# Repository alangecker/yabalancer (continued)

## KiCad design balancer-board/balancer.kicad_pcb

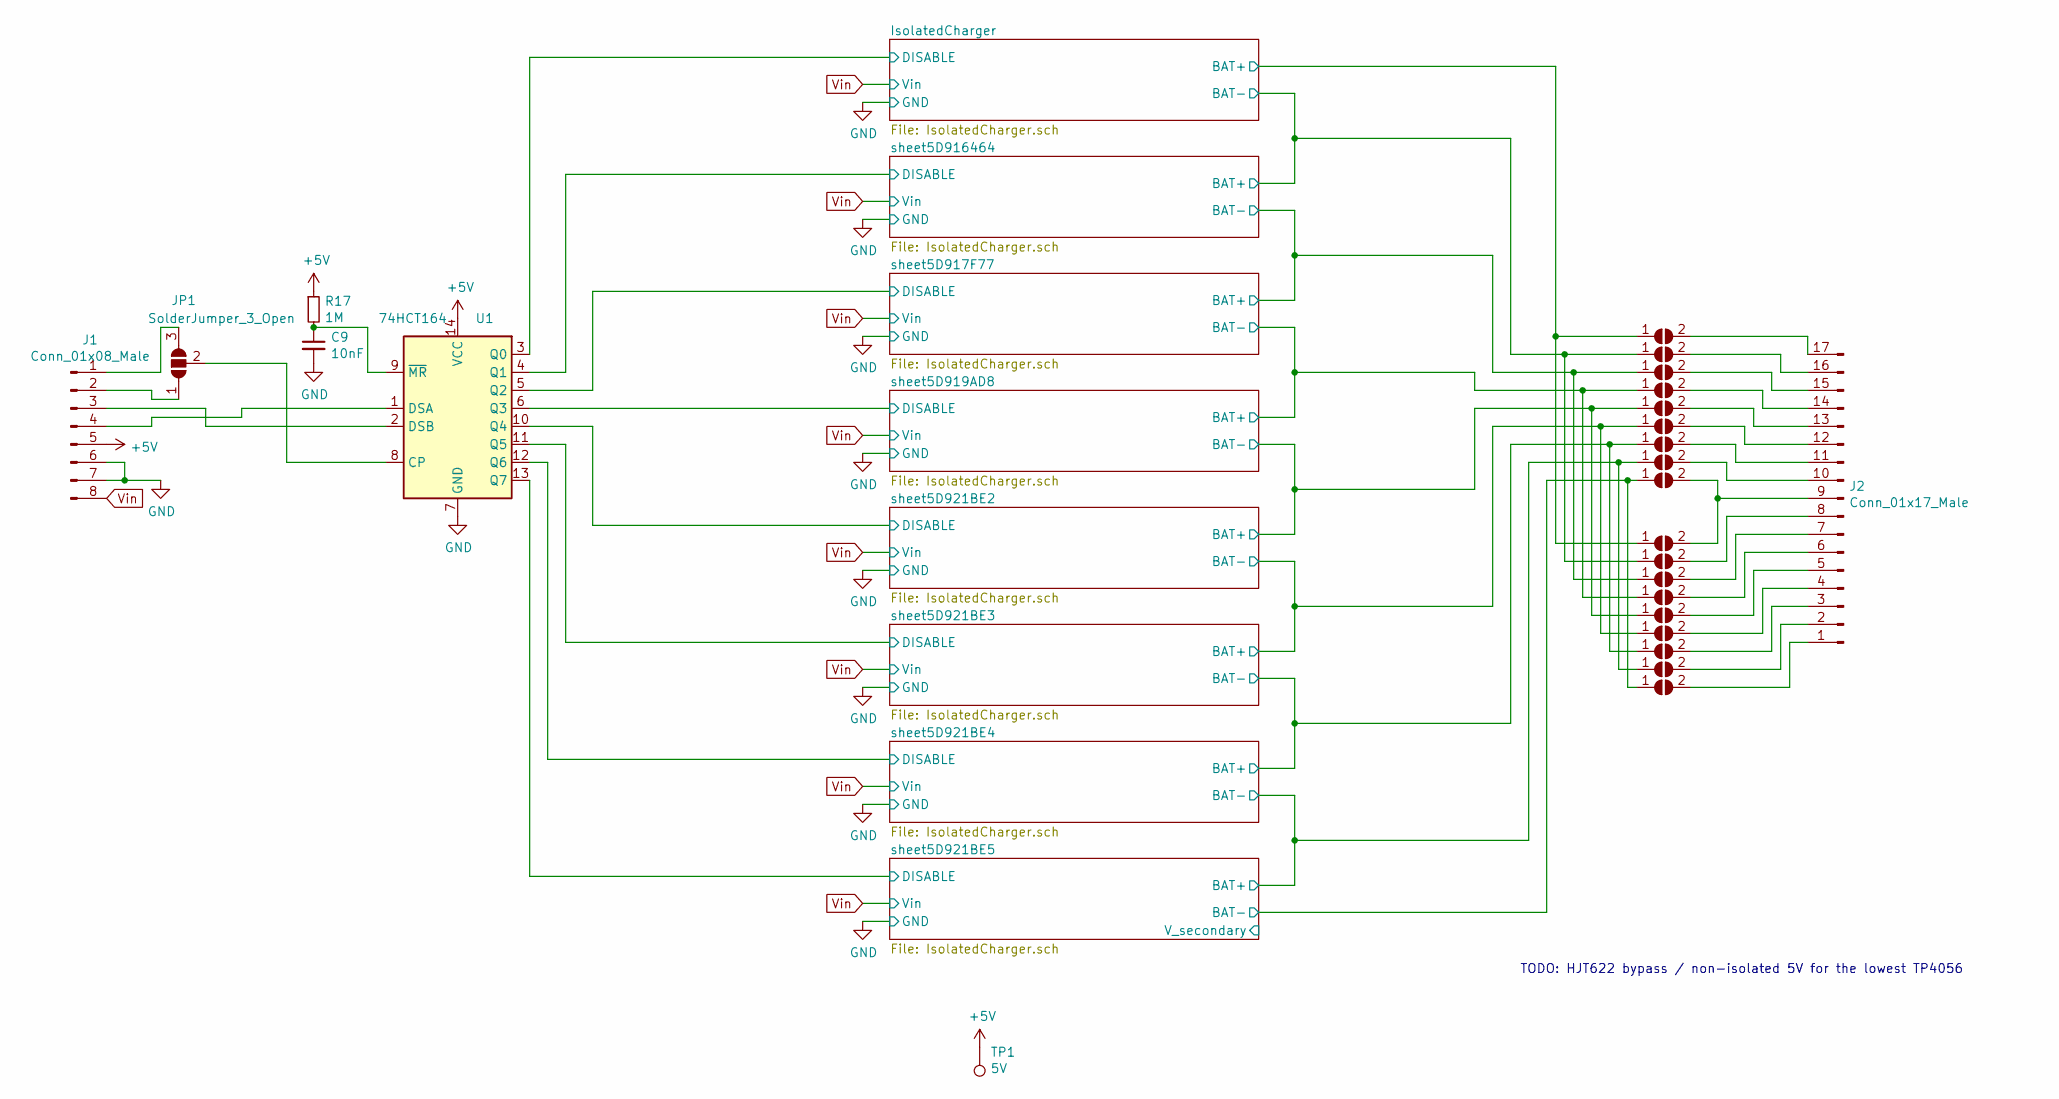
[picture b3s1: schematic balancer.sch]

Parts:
C9: 10nF; C_0805_2012Metric_Pad1.15x1.40mm_HandSolder
J1: Conn_01x08_Male; PinHeader_1x08_P2.54mm_Vertical
J2: Conn_01x17_Male; PinHeader_1x17_P2.54mm_Vertical
JP1: SolderJumper_3_Open; SolderJumper-3_P1.3mm_Open_RoundedPad1.0x1.5mm
JP2, JP3, JP4, JP5, JP6, JP7, JP8, JP9, JP10, JP11, JP12, JP13, JP14, JP15, JP16, JP17, JP18, JP19: SolderJumper_2_Open; SolderJumper-2_P1.3mm_Open_Pad1.0x1.5mm
R17: 1M; R_0805_2012Metric_Pad1.15x1.40mm_HandSolder
TP1: 5V; TestPoint_THTPad_2.5x2.5mm_Drill1.2mm
U1: 74HCT164; SO-14

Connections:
+5V: J1.5, R17.1, TP1.1, U1.14 (VCC)
/IsolatedCharger/BAT+: JP2.1 (A), JP11.1 (A); also elsewhere on the board
/IsolatedCharger/DISABLE: U1.3 (Q0); also elsewhere on the board
/sheet5D917F77/BAT+: JP4.1 (A), JP13.1 (A); also elsewhere on the board
/sheet5D917F77/DISABLE: U1.5 (Q2); also elsewhere on the board
/sheet5D919AD8/BAT+: JP5.1 (A), JP14.1 (A); also elsewhere on the board
/sheet5D919AD8/DISABLE: U1.6 (Q3); also elsewhere on the board
/sheet5D921BE2/BAT+: JP6.1 (A), JP15.1 (A); also elsewhere on the board
/sheet5D921BE2/DISABLE: U1.10 (Q4); also elsewhere on the board
/sheet5D921BE3/BAT+: JP7.1 (A), JP16.1 (A); also elsewhere on the board
/sheet5D921BE3/DISABLE: U1.11 (Q5); also elsewhere on the board
/sheet5D921BE4/BAT+: JP8.1 (A), JP17.1 (A); also elsewhere on the board
/sheet5D921BE4/DISABLE: U1.12 (Q6); also elsewhere on the board
/sheet5D921BE5/BAT+: JP9.1 (A), JP18.1 (A); also elsewhere on the board
/sheet5D921BE5/BAT-: JP10.1 (A), JP19.1 (A); also elsewhere on the board
/sheet5D921BE5/DISABLE: U1.13 (Q7); also elsewhere on the board
/sheet5D916464/BAT+: JP3.1 (A), JP12.1 (A); also elsewhere on the board
/sheet5D916464/DISABLE: U1.4 (Q1); also elsewhere on the board
GND: C9.2, J1.6, J1.7, U1.7 (GND); also elsewhere on the board
unnamed: C9.1, R17.2, U1.9 (~MR)
unnamed: J1.1, JP1.3 (B)
unnamed: J1.2, JP1.1 (A)
unnamed: J1.3, U1.2 (DSB)
unnamed: J1.4, U1.1 (DSA)
unnamed: J2.1, JP19.2 (B)
unnamed: J2.2, JP18.2 (B)
unnamed: J2.3, JP17.2 (B)
unnamed: J2.4, JP16.2 (B)
unnamed: J2.5, JP15.2 (B)
unnamed: J2.6, JP14.2 (B)
unnamed: J2.7, JP13.2 (B)
unnamed: J2.8, JP12.2 (B)
unnamed: J2.9, JP10.2 (B), JP11.2 (B)
unnamed: J2.10, JP9.2 (B)
unnamed: J2.11, JP8.2 (B)
unnamed: J2.12, JP7.2 (B)
unnamed: J2.13, JP6.2 (B)
unnamed: J2.14, JP5.2 (B)
unnamed: J2.15, JP4.2 (B)
unnamed: J2.16, JP3.2 (B)
unnamed: J2.17, JP2.2 (B)
unnamed: JP1.2 (C), U1.8 (CP)
Vin: J1.8; also elsewhere on the board

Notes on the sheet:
TODO: HJT622 bypass / non-isolated 5V for the lowest TP4056

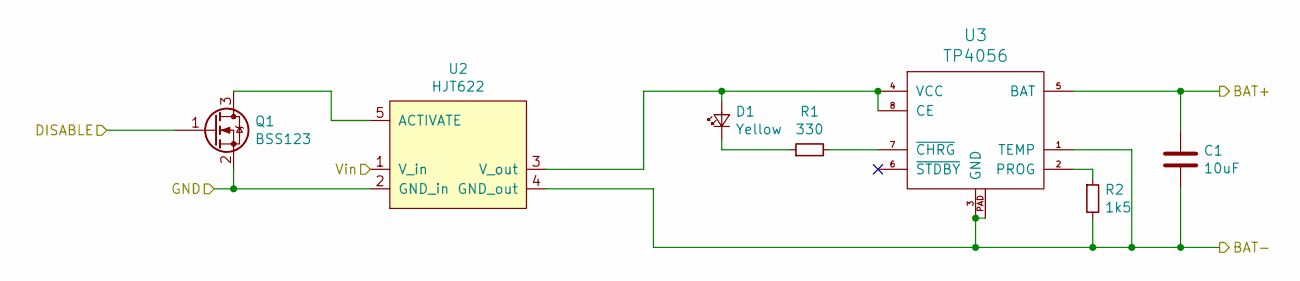
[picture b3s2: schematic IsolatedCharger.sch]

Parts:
C1: 10uF; C_0805_2012Metric
D1: Yellow; LED_D5.0mm_Horizontal_O1.27mm_Z15.0mm
Q8: BSS123; SOT-23
R1: 330; R_0805_2012Metric
R2: 1k5; R_0805_2012Metric
U2: HJT622
U3: TP4056; SOP-8_3.76x4.96mm_P1.27mm

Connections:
/IsolatedCharger/BAT+: C1.1, U3.5 (BAT); also elsewhere on the board
/sheet5D921BE5/DISABLE: Q8.1 (G); also elsewhere on the board
/sheet5D916464/BAT+: C1.2, R2.2, U2.4 (GND_out), U3.1 (TEMP), U3.3 (GND), U3.PAD; also elsewhere on the board
GND: Q8.2 (S), U2.2 (GND_in); also elsewhere on the board
unnamed: D1.1 (K), R1.1
unnamed: D1.2 (A), U2.3 (V_out), U3.4 (VCC), U3.8 (CE)
unnamed: R1.2, U3.7 (~CHRG)
unnamed: R2.1, U3.2 (PROG)
Vin: U2.1 (V_in); also elsewhere on the board

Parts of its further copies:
C2, C3, C4, C5, C6, C7, C8: 10uF; C_0805_2012Metric
D2, D3, D4, D5, D6, D7, D8: Yellow; LED_D5.0mm_Horizontal_O1.27mm_Z15.0mm
R3, R5, R7, R9, R11, R13, R15: 330; R_0805_2012Metric
R4, R6, R8, R10, R12, R14, R16: 1k5; R_0805_2012Metric
U4, U6, U8, U10, U12, U14, U16: HJT622
U5, U7, U9, U11, U13, U15, U17: TP4056; SOP-8_3.76x4.96mm_P1.27mm

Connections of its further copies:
/sheet5D917F77/BAT+: C2.2, C3.1, R4.2, U4.4 (GND_out), U5.1 (TEMP), U5.3 (GND), U7.5 (BAT); also elsewhere on the board
/sheet5D919AD8/BAT+: C3.2, C4.1, R6.2, U6.4 (GND_out), U7.1 (TEMP), U7.3 (GND), U9.5 (BAT); also elsewhere on the board
/sheet5D921BE2/BAT+: C4.2, C5.1, R8.2, U8.4 (GND_out), U9.1 (TEMP), U9.3 (GND), U11.5 (BAT); also elsewhere on the board
/sheet5D921BE3/BAT+: C5.2, C6.1, R10.2, U10.4 (GND_out), U11.1 (TEMP), U11.3 (GND), U13.5 (BAT); also elsewhere on the board
/sheet5D921BE4/BAT+: C6.2, C7.1, R12.2, U12.4 (GND_out), U13.1 (TEMP), U13.3 (GND), U15.5 (BAT); also elsewhere on the board
/sheet5D921BE5/BAT+: C7.2, C8.1, R14.2, U14.4 (GND_out), U15.1 (TEMP), U15.3 (GND), U17.5 (BAT); also elsewhere on the board
/sheet5D921BE5/BAT-: C8.2, R16.2, U16.4 (GND_out), U17.1 (TEMP), U17.3 (GND); also elsewhere on the board
/sheet5D916464/BAT+: C2.1, U5.5 (BAT); also elsewhere on the board
GND: U4.2 (GND_in), U6.2 (GND_in), U8.2 (GND_in), U10.2 (GND_in), U12.2 (GND_in), U14.2 (GND_in), U16.2 (GND_in); also elsewhere on the board
unnamed: D2.1 (K), R3.1
unnamed: D2.2 (A), U4.3 (V_out), U5.4 (VCC), U5.8 (CE)
unnamed: D3.1 (K), R5.1
unnamed: D3.2 (A), U6.3 (V_out), U7.4 (VCC), U7.8 (CE)
unnamed: D4.1 (K), R7.1
unnamed: D4.2 (A), U8.3 (V_out), U9.4 (VCC), U9.8 (CE)
unnamed: D5.1 (K), R9.1
unnamed: D5.2 (A), U10.3 (V_out), U11.4 (VCC), U11.8 (CE)
unnamed: D6.1 (K), R11.1
unnamed: D6.2 (A), U12.3 (V_out), U13.4 (VCC), U13.8 (CE)
unnamed: D7.1 (K), R13.1
unnamed: D7.2 (A), U14.3 (V_out), U15.4 (VCC), U15.8 (CE)
unnamed: D8.1 (K), R15.1
unnamed: D8.2 (A), U16.3 (V_out), U17.4 (VCC), U17.8 (CE)
unnamed 58: U4.5 (ACTIVATE); also elsewhere on the board
unnamed 59: U6.5 (ACTIVATE); also elsewhere on the board
unnamed 60: U8.5 (ACTIVATE); also elsewhere on the board
unnamed 61: U10.5 (ACTIVATE); also elsewhere on the board
unnamed 62: U12.5 (ACTIVATE); also elsewhere on the board
unnamed 63: U14.5 (ACTIVATE); also elsewhere on the board
unnamed: R3.2, U5.7 (~CHRG)
unnamed: R4.1, U5.2 (PROG)
unnamed: R5.2, U7.7 (~CHRG)
unnamed: R6.1, U7.2 (PROG)
unnamed: R7.2, U9.7 (~CHRG)
unnamed: R8.1, U9.2 (PROG)
unnamed: R9.2, U11.7 (~CHRG)
unnamed: R10.1, U11.2 (PROG)
unnamed: R11.2, U13.7 (~CHRG)
unnamed: R12.1, U13.2 (PROG)
unnamed: R13.2, U15.7 (~CHRG)
unnamed: R14.1, U15.2 (PROG)
unnamed: R15.2, U17.7 (~CHRG)
unnamed: R16.1, U17.2 (PROG)
Vin: U4.1 (V_in), U6.1 (V_in), U8.1 (V_in), U10.1 (V_in), U12.1 (V_in), U14.1 (V_in), U16.1 (V_in); also elsewhere on the board

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
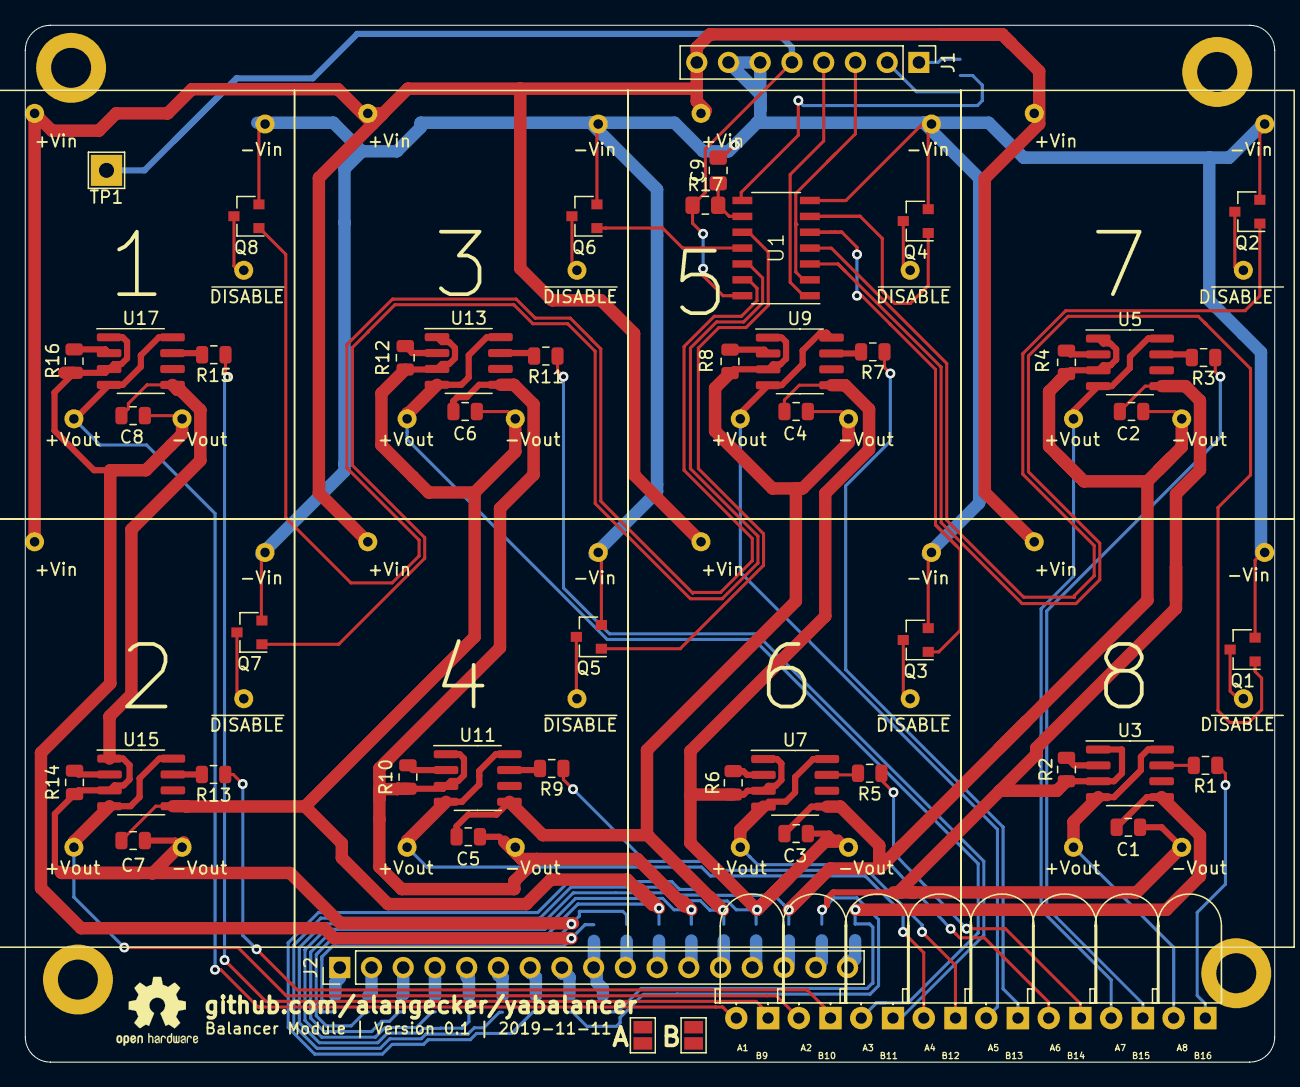
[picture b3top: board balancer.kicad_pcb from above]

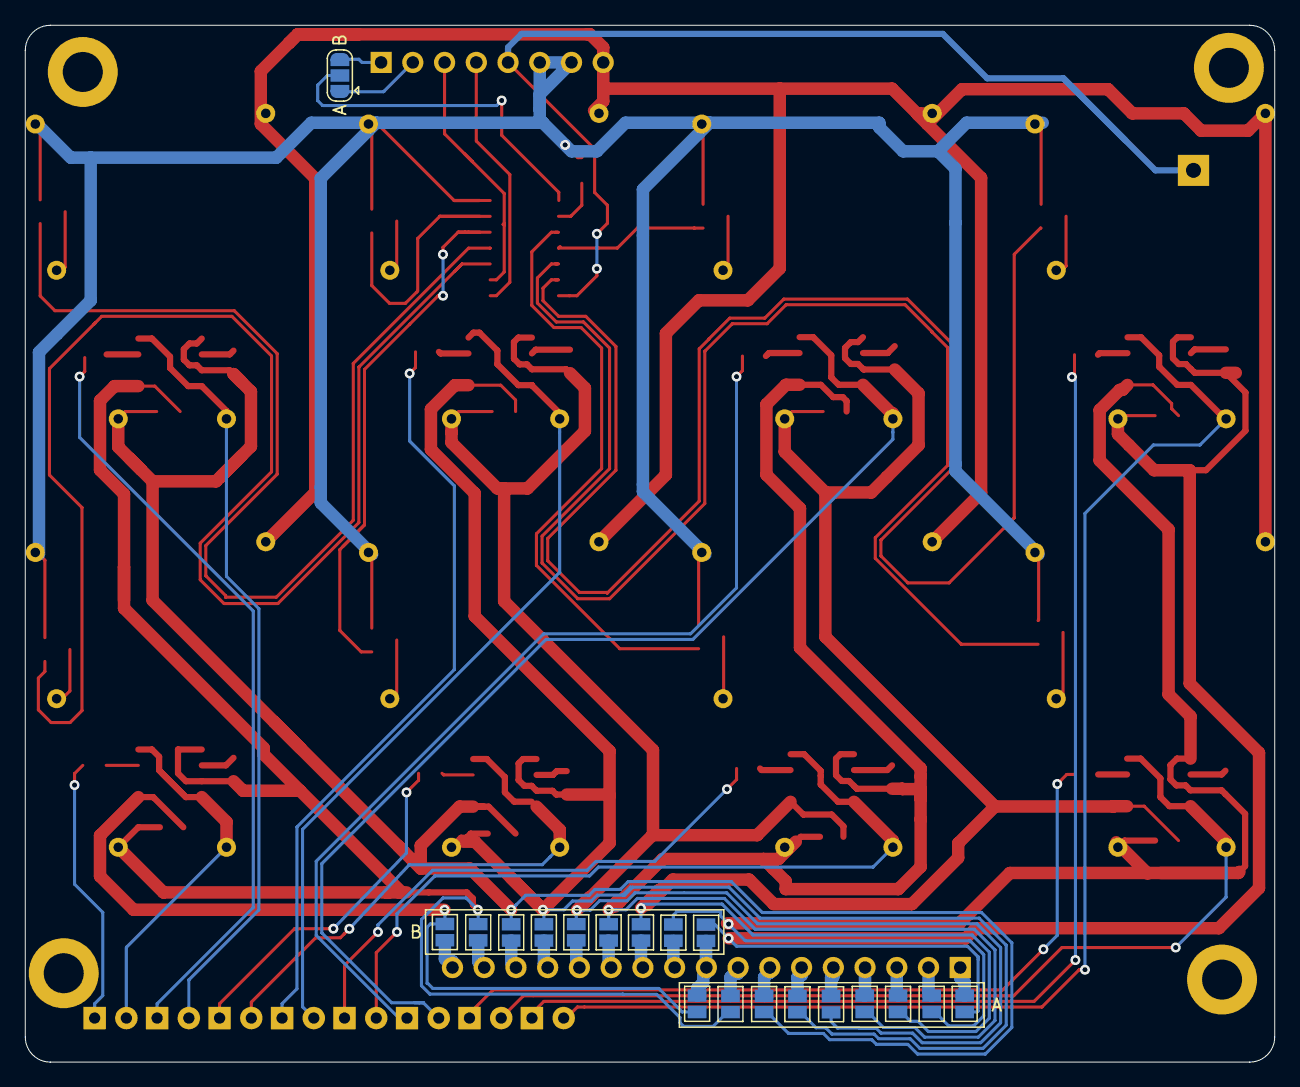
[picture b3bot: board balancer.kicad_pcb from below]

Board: 2 copper layers, 100.0 x 83.0 mm, 81 parts (19 on the bottom side), 83 nets.

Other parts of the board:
Q1, Q2, Q3, Q4, Q5, Q6, Q7: AO3400; SOT-23

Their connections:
/IsolatedCharger/DISABLE: Q1.1; also elsewhere on the board
/sheet5D917F77/DISABLE: Q3.1; also elsewhere on the board
/sheet5D919AD8/DISABLE: Q4.1; also elsewhere on the board
/sheet5D921BE2/DISABLE: Q5.1; also elsewhere on the board
/sheet5D921BE3/DISABLE: Q6.1; also elsewhere on the board
/sheet5D921BE4/DISABLE: Q7.1; also elsewhere on the board
/sheet5D916464/DISABLE: Q2.1; also elsewhere on the board
GND: Q1.2, Q2.2, Q3.2, Q4.2, Q5.2, Q6.2, Q7.2; also elsewhere on the board
unnamed 58: Q2.3; also elsewhere on the board
unnamed 59: Q3.3; also elsewhere on the board
unnamed 60: Q4.3; also elsewhere on the board
unnamed 61: Q5.3; also elsewhere on the board
unnamed 62: Q6.3; also elsewhere on the board
unnamed 63: Q7.3; also elsewhere on the board

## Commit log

2019-10-20 multiple changes
2019-11-11 v0.1
